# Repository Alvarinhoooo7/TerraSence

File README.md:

<div align="center">
  <picture>
    <source media="(prefers-color-scheme: dark)" srcset="Logo/Logo/terrasense-wordmark-dark.svg" />
    
  </picture>
</div>

# TerraSense

TerraSense es un proyecto de instrumento portátil y aplicación móvil para medir suelo y ambiente, interpretar las lecturas según la etapa del cultivo y orientar qué revisar en el campo. Está dirigido a agricultores y asesores que necesitan consultar y guardar mediciones, incluso donde no hay cobertura de internet.

**El proyecto está en desarrollo.** La app implementa la captura por Bluetooth, la evaluación local y el historial. El firmware ya lee la sonda de suelo por Modbus: en banco entregó 1.000 de 1.000 lecturas sin error de verificación de redundancia cíclica (31-10-2026), con la sonda al aire. Lo pendiente es la exactitud de esas lecturas en agua y en tierra, que se cierra con la campaña de laboratorio, y la validación en campo.

## Por qué TerraSense

TerraSense no es un sensor de suelo ni un nodo de monitoreo enterrado: es una **sonda portátil multivariable de diagnóstico agronómico**. Viaja con la persona, mide donde la persona decide y entrega diez variables del punto de medición en el mismo instante, terminando en una orientación o plan de acción según la fase del cultivo y la especie. Esa combinación es la que no existe en el mercado actual.

La propuesta se ordena en tres clases de valor, y conviene no mezclarlas porque cada una se sostiene con evidencia distinta: la **funcional** (qué permite hacer el instrumento que hoy no se puede), la **económica** (qué cuesta sostener esa información en el tiempo) y la **emocional** (qué incertidumbre le quita de encima al productor). El texto canónico de la propuesta, con esas tres clases y la clasificación de cada atributo en paridad o diferencia, vive en [el capítulo III del informe de la Evaluación 2](Evaluacion/Evaluacion%202/INFORME%202.md#la-propuesta-de-valor); lo que sigue es su resumen.

| | Laboratorio de suelos | Nodo fijo de monitoreo | Medidor portátil de 1 a 4 variables | **TerraSense** |
|---|---|---|---|---|
| Puntos que se pueden medir | sólo los que se pagan | uno por nodo instalado | cualquiera | **cualquiera, con su ubicación registrada** |
| Costo de la medición siguiente | el precio de otra muestra | otro nodo para cubrir otro punto | cero | **cero** |
| Variables por lectura | según el análisis contratado | las del nodo | 1 a 4 | **10: 7 del suelo y 3 del ambiente** |
| Qué recibe el agricultor | concentraciones trazables, en días | series de tiempo y alertas del punto | un valor numérico | **las diez variables con semáforo y un plan de acción por fase del cultivo** |
| Sin cobertura de internet | logística de envío | requiere red permanente | funciona | **mide, diagnostica, georreferencia y guarda** |
| Suscripción mensual | se paga por muestra | habitual en la plataforma | no | **ninguna, y las mediciones son del agricultor** |
| Memoria del punto medido | informes sueltos | del punto fijo | no deja registro | **historial con fecha, ubicación y evaluación** |

Las ventajas no son atributos declarados: son consecuencias de cómo está construido el sistema.

1. **Mide donde el agricultor decide.** El campo no es homogéneo. Un nodo fijo describe con mucho detalle un solo punto; una sonda portátil describe el campo entero. Es arquitectura, no una característica que se pueda igualar bajando el precio.
2. **Diez variables en una sola inserción.** Siete del suelo —humedad, temperatura, conductividad eléctrica, pH, nitrógeno, fósforo y potasio— y tres del ambiente —temperatura, humedad y presión del aire—, todas del mismo punto y del mismo instante. Los medidores portátiles con que se compara entregan entre tres y cuatro.
3. **Entrega un plan de acción, no un número.** El motor agronómico corre completo en el teléfono y traduce la medición en qué revisar, por qué y en qué orden. Un valor de conductividad no dice nada a quien no lo interpreta: la diferencia entre el dato y la decisión es todo el producto.
4. **La medición siguiente no cuesta nada.** Sin cobro por lectura ni suscripción, el costo marginal de volver a medir es cero. Eso cambia la conducta: se mide antes y después de fertilizar, en varios sectores, durante toda la temporada.
5. **Funciona sin cobertura.** Medir, diagnosticar, georreferenciar y guardar ocurren sin red; la nube sólo respalda después. En un campo sin señal, un producto que necesite conexión para interpretar no sirve.
6. **Deja memoria del campo.** Cada medición queda con su fecha, su ubicación y su evaluación, de modo que la segunda temporada se compara con la primera.

**Complemento del laboratorio, no su reemplazo.** Un análisis acreditado entrega concentraciones trazables de los puntos que se pagan, una o dos veces por temporada. TerraSense aporta lo que ese análisis no puede costear: la repetición. Medir el mismo punto antes y después de fertilizar, medir varios sectores el mismo día y repetir la lectura cuantas veces se quiera permite ponderar el comportamiento del campo sobre muchas mediciones, en lugar de inferirlo de una sola muestra. No tiene la exactitud del laboratorio en una medición aislada y no pretende tenerla: lo complementa, porque además termina donde el informe de laboratorio no llega, que es en un plan de acción según la fase del cultivo. Lo mismo vale para el asesor agronómico, cuyo criterio el equipo confirma o corrige con datos del propio suelo, y para el nodo fijo, que da continuidad en un punto mientras la sonda cubre el campo entero. El laboratorio fija el punto de referencia; TerraSense sigue su evolución entre un análisis y el siguiente.

**Qué nos diferencia y qué sólo nos iguala.** De los atributos del producto, cuatro son diferencia frente a toda la competencia comparable: la interpretación por etapa fenológica y especie, la orientación de manejo como salida del sistema, las diez variables de una sola inserción y la trazabilidad documental del criterio agronómico con su catálogo de cultivos chileno. Los demás integran el producto y se comunican como parte de él, nunca como su diferencia: la portabilidad es condición de la categoría, y la aplicación propia, la georreferenciación, el uso sin conexión y la ausencia de suscripción **también los ofrecen los medidores portátiles con que competimos**. La ausencia de suscripción es diferencia frente al laboratorio, que cobra por muestra, y frente al monitoreo remoto, que cobra plataforma mensual; no frente a Hanna ni a Bluelab, que tampoco cobran cuota. La clasificación completa está en la tabla de paridad y diferencia del [texto canónico](Evaluacion/Evaluacion%202/INFORME%202.md#la-propuesta-de-valor).

## Cómo funciona

1. **El equipo reúne las lecturas.** El diseño integra una sonda de suelo y un sensor ambiental BME280 con un ESP32 que se comunica con el teléfono por Bluetooth de bajo consumo (BLE).
2. **La app interpreta la medición.** El usuario elige la etapa del cultivo y, cuando corresponde, puede indicar la especie. El motor agronómico aplica reglas locales, explica las condiciones que requieren atención y señala lo que no puede evaluar con los datos disponibles.
3. **El resultado queda guardado.** La app conserva la lectura y su evaluación en el teléfono y las sincroniza con Supabase cuando hay conexión. Si el usuario incluye su ubicación, también puede consultar el pronóstico como apoyo para organizar labores.
4. **El backoffice permite dar soporte.** La cuenta de soporte administra equipos y accesos desde la web.

```mermaid
flowchart LR
    S[Sonda de suelo] -->|RS-485| E[ESP32]
    B[Sensor ambiental BME280] --> E
    E <-->|Bluetooth| A[App móvil]
    C[Servicio de pronóstico] -.->|Internet| A
    A <-->|Sincronización| D[(Supabase)]
    W[Backoffice de soporte] <--> D
```

La medición y la evaluación local están diseñadas para funcionar sin internet después de configurar la cuenta y vincular el equipo. El pronóstico, la gestión de accesos y el respaldo en la nube requieren conexión. Las recomendaciones son orientativas y dependen de la calidad de las lecturas y de los criterios disponibles para cada cultivo.

## Dónde encontrar cada parte

| Módulo | Qué contiene |
|---|---|
| [App móvil](App/README.md) | Funcionamiento de la app, flujo de pantallas, motor agronómico y puesta en marcha. |
| [Firmware](Firmware/README.md) | Programa del ESP32, comunicación con el teléfono y estado de integración de los sensores. |
| [Hardware](PCB/README.md) | Esquemáticos, placa electrónica, alimentación y carcasa. |
| [Backoffice web](Web/README.md) | Herramientas de soporte y ejecución de la web. |
| [Supabase](supabase/README.md) | Base de datos, autenticación, permisos y sincronización. |
| [Documentación](docs/README.md) | Informes, contratos técnicos y plan de validación. |

Para ejecutar el software, sigue la puesta en marcha de [App](App/README.md#desarrollo-local) o de [Web](Web/README.md). Cada módulo documenta su propia configuración.

Lo que llega a `main`, y cada pull request, pasa por el [workflow de verificación](.github/workflows/verificacion.yml): regenera el modelo financiero y corre sus pruebas, revisa los enlaces y diagramas de la documentación, y ejecuta las pruebas de la app y las del backoffice con su construcción. Además guarda dos reglas que no se deducen leyendo el código: que ningún archivo generado se haya editado a mano y que el informe entregable se lea sin acceso al repositorio.

<!-- FINANZAS:INICIO -->

## Modelo económico

El proyecto contempla la venta del equipo, con la app y la evaluación local sin suscripción. El precio se deriva de la estructura completa de costos y de la utilidad exigida por el modelo.

Los supuestos, el financiamiento y los resultados de viabilidad se consultan en el [modelo económico](docs/MODELO_ECONOMICO.md) y los [resultados financieros](docs/RESULTADOS_FINANCIEROS.md). Las cifras se regeneran con `python finanzas/modelo.py`.

<!-- FINANZAS:FIN -->

---

Proyecto de título de Ingeniería en Electrónica y Sistemas Inteligentes — INACAP.

Autores: Álvaro Villena y Alan Escobar.

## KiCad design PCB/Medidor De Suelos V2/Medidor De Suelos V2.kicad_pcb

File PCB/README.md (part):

# 🔌 TerraSense · PCB V2

Especificación del hardware del instrumento portátil de medición de suelo: placa portadora, árbol de alimentación, control y periféricos. Este documento es la fuente para dibujar el esquemático y rutear la placa.

> ### 🛑 Estado de verificación — leer antes de usar este documento
>
> **Describe un diseño en curso, no un producto verificado.** Las secciones 4 a 9 se escribieron antes de dibujar el esquemático y conservan designadores y nets antiguos: **cuando difieran, mandan el esquemático de KiCad y [`Firmware/pines.h`](../Firmware/pines.h)**. El mapa de pines de la sección 5.7 ya está alineado con ambos.
>
> | Afirmación | Estado real |
> | :--- | :--- |
> | Placa ruteada | **Sí.** Esquemático y ruteo en `Medidor De Suelos V2/`. Primer lote de 5 placas sin ensamblar pedido a JLCPCB; aún no se arma ni se prueba |
> | Firmware | **Existe en [`Firmware/`](../Firmware/README.md)**: vinculación BLE, LEDs, buzzer, trama de 20 bytes y lectura Modbus de la sonda, esta última sin ensayo en banco |
> | Mapa de registros de la sonda | **Coincide con el manual del fabricante** de la muestra adquirida (ComWinTop CWT-Soil-NPKPHCTH-S). Falta la captura real en banco |
> | BLE 5.0 | El ESP32-WROOM-32E especifica **Bluetooth 4.2 BR/EDR y BLE**. La certificación del módulo no acredita el equipo terminado |
> | Consumo en reposo y autonomía | **No se declaran en la V2.** Ver sección 5.9 |
> | IP67 y peso bajo 280 g | **Objetivos de diseño sin ensayo.** No hay actas ni pesaje del conjunto |
> | Sonda operando a 5 V | Solo puede afirmarse del **SKU y variante validados**, que aún no se adquieren |
>
> Las cifras de componentes y costos viven en la lista `bom` de [`finanzas/supuestos.json`](../finanzas/supuestos.json) y se publican en [`BOM_TerraSense.xlsx`](BOM_TerraSense.xlsx), que regenera `python finanzas/modelo.py`. **No editar ese Excel a mano.**

---

## 📑 Tabla de Contenidos

- [1. Alcance de la V2](#1-alcance-de-la-v2)
- [2. Especificaciones generales](#2-especificaciones-generales)
- [3. Arquitectura y nets del sistema](#3-arquitectura-y-nets-del-sistema)
- [4. Guía de Implementación del Esquemático](#4-guía-de-implementación-del-esquemático)
- [5. Puntos de prueba y medición](#5-puntos-de-prueba-y-medición)
- [6. Fabricación de la PCB y Diseño mecánico](#6-fabricación-de-la-pcb-y-diseño-mecánico)
- [7. Decisiones de Diseño y Detalles Técnicos (Rationale)](#7-decisiones-de-diseño-y-detalles-técnicos-rationale)
- [8. Orden de trabajo y pendientes](#8-orden-de-trabajo-y-pendientes)
- [9. Netlist completa](#9-netlist-completa)

---

## 1. Alcance de la V2

La V2 es una **placa portadora**: no integra el silicio, sino que sostiene y conecta tres módulos comerciales más la electrónica discreta que los une.

| Módulo | Qué aporta |
| :--- | :--- |
| DevKit ESP32-WROOM-32 | Microcontrolador, radio BLE, regulador de 3,3 V y USB-UART |
| **`LX-LCBST`**, PCB combinada USB-C | Carga de la celda con sus protecciones y elevación a 5,0 V |
| Módulo BME280 I²C | Temperatura del aire, humedad relativa y presión |

### 1.1. Decisiones cerradas

| Decisión | Valor | Motivo |
| :--- | :--- | :--- |
| Microcontrolador | **DevKit ESP32-WROOM-32**, no módulo desnudo | Evita rutear LDO, USB-UART y auto-reset en la portadora |
| Carga con el equipo apagado | **Sí** | Define dónde va `SW1`: después del módulo, nunca en serie con la celda |
| USB al exterior | **Solo el USB-C del módulo de carga** | El micro-USB de la DevKit queda interno |
| Tercer pin del conector de batería | **NC**, no conectado | |
| Divisor de batería | **Conmutado por MOSFET**, no fijo | Evita dejar tensión sobre una entrada sin alimentar |
| Consumo en reposo | **No se declara** | La DevKit consume miliamperios; `SW1` lo resuelve apagando |
| Trama BLE | **20 bytes, formato único** | Contrato de la sección 6.9 |

> La elección de DevKit es **propia de esta versión**. El proyecto está definido sobre el módulo WROOM-32 desnudo, que es lo que costea el BOM. Volver al módulo desnudo obliga a agregar a la portadora el regulador de 3,3 V, el USB-UART y el circuito de auto-reset.

### 1.2. Contenido de la carpeta

| Ruta | Qué es |
| :--- | :--- |
| `README.md` | Este documento |
| `BOM_TerraSense.xlsx` | Lista de materiales, **generada**; no editar a mano |
| `Medidor De Suelos V2/` | Proyecto KiCad de la V2: esquemático y ruteo. **Fuente de verdad del hardware** |
| `V1/` | Prototipo anterior, congelado. No se edita ni se usa como referencia de diseño |
| `V3/` | Placa del instrumento del informe 2 (90 × 64 mm): esquemático con circuitos integrados soldados y placa ruteada en dos capas con planos de masa. Local, fuera de git; no está liberada a fabricación |

Las vistas de la V3 y los anexos C y D se regeneran con `python finanzas/figuras_e2.py`, que toma los renders de la placa con `kicad-cli`. El estado eléctrico y mecánico pendiente está en el [plan de implementación del informe 2](<../Evaluacion/Evaluacion 2/PLAN DE IMPLEMENTACION.md>). La lista de materiales y los costos se mantienen por decisión del proyecto.

---

## 2. Especificaciones generales

| Parámetro | Valor de diseño | Justificación |
| :--- | :--- | :--- |
| **Microcontrolador** | DevKit ESP32-WROOM-32 | Doble núcleo a 240 MHz, 520 KB SRAM, 4 MB de flash. [Ficha Espressif](https://documentation.espressif.com/esp32-wroom-32e_esp32-wroom-32ue_datasheet_en.html): **Bluetooth 4.2 BR/EDR y BLE**, no 5.0 |
| **Sonda de suelo** | Industrial 7 en 1, RS-485 Modbus RTU | ComWinTop CWT-Soil-NPKPHCTH-S. Alimentación **4,5 – 30 V DC**, 0,5 W como máximo a 24 V, IP68, cable de 2 m; electrodos de aleación anticorrosión, grado de acero por confirmar |
| **Alimentación de la sonda** | **5,0 V DC** conmutados | Operación directa sin elevar a 12 V; menor estrés térmico y menor consumo |
| **Sensor ambiental** | BME280 I²C a 3,3 V | Temperatura del aire, humedad relativa y presión en el punto de lectura |
| **Transceptor de bus** | SP3485 a 3,3 V | Diferencial industrial semidúplex, sin desplazadores de nivel |
| **Batería** | LiPo 1S 3,7 V, 2.000 mAh con PCM | Formato prismático plano, ~35 g, sin portaceldas |
| **Carga y elevación** | Módulo **`LX-LCBST`** | Resuelve carga, protección y elevación a 5 V en un submódulo |
| **Encendido** | Interruptor rocker SPST | Corta el consumo entre usos |
| **Formato** | Instrumento portátil de mano | Inserción manual directa en el suelo |

---

## 3. Arquitectura y nets del sistema

```text
 ┌─────────────────────────────────────────────────────────────────────────────┐
 │                    DIAGRAMA DE BLOQUES — TerraSense V2                      │
 └─────────────────────────────────────────────────────────────────────────────┘

   [ USB-C exterior ]
          │
          ▼
  ┌───────────────────────────────┐        ┌──────────────────────────┐
  │  MOD1  LX-LCBST carga+boost   │◄───────┤ BT1 LiPo 1S 2000 mAh     │
  │  • Cargador con protecciones  │  VBAT  │ P1 / P2 pads soldados    │
  │  • Elevador 3,7 V ──► 5,0 V   │────────┤ F1 fusible 1 A · JP1     │
  │                               │        │ D1 M7 crowbar a GND      │
  └───────────────┬───────────────┘        └──────────────────────────┘
                  │ 5 V
                  ▼
            [ SW1 rocker ]
                  │
                  ▼  +5V ──────────────────────────────┐
  ┌───────────────┴───────────────┐                    │
  │  U1  DevKit ESP32-WROOM-32    │                    ▼
  │  VIN ◄── +5V   (C3, C4)       │          [ Q1 P-MOSFET power gate ]
  │  3V3 ──► +3V3  (C5, C6)       │             (mandado por GPIO5 vía Q2)
  └──┬─────────────┬──────────┬───┘                    │
     │             │          │                        ▼  5V_SONDA
     │ I²C         │ UART2    │ ADC                    │
     ▼             ▼          ▼                        │
 [ U3 BME280 ]  [ U2 SP3485 ] [ Divisor R9/R10 ]       │
       3V3         3V3          conmutado por Q3       │
                    │ A/B                              │
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
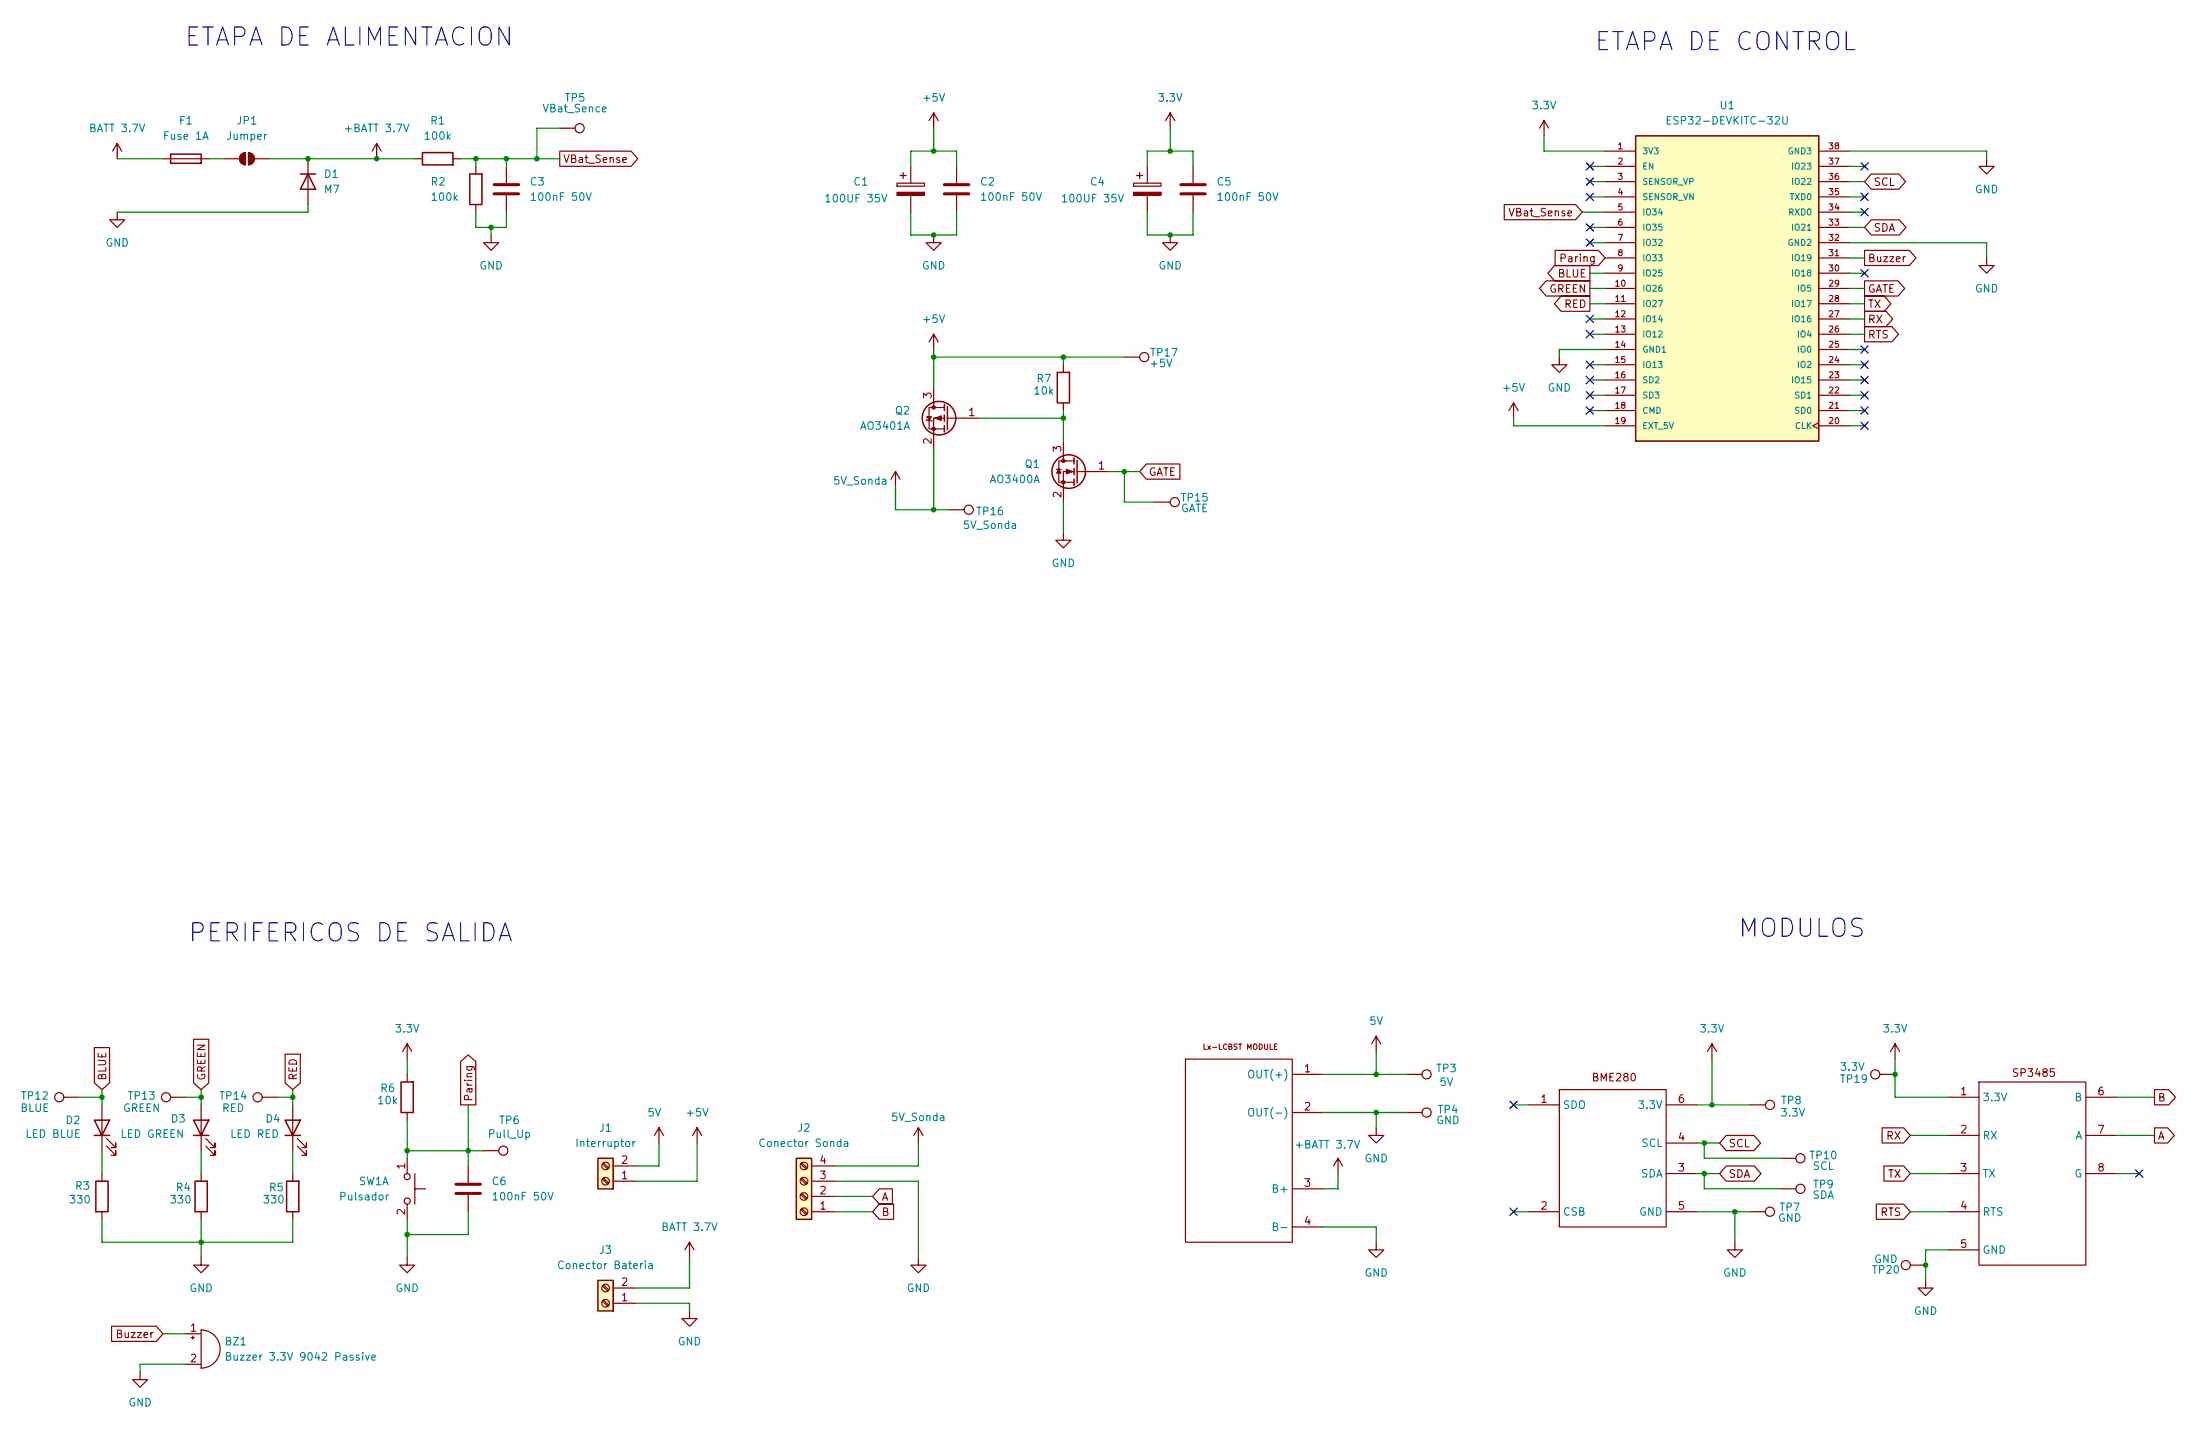
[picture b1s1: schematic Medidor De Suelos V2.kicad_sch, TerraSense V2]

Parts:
BZ1: Buzzer 3.3V 9042 Passive; MagneticBuzzer_CUI_CST-931RP-A
C1, C4: 100UF 35V; CP_Elec_6.3x7.7
C2, C3, C5, C6: 100nF 50V; C_1206_3216Metric_Pad1.33x1.80mm_HandSolder
D1: M7; D_SMA
D2: LED BLUE; LED_0603_1608Metric_Pad1.05x0.95mm_HandSolder
D3: LED GREEN; LED_0603_1608Metric_Pad1.05x0.95mm_HandSolder
D4: LED RED; LED_0603_1608Metric_Pad1.05x0.95mm_HandSolder
F1: Fuse 1A; Fuse_0603_1608Metric
J1: Interruptor; TerminalBlock_MetzConnect_Type055_RT01502HDWU_1x02_P5.00mm_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
J2: Conector Sonda; TerminalBlock_MetzConnect_Type055_RT01504HDWU_1x04_P5.00mm_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
J3: Conector Bateria; TerminalBlock_MetzConnect_Type055_RT01502HDWU_1x02_P5.00mm_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
JP1: Jumper; SolderJumper-2_P1.3mm_Open_Pad1.0x1.5mm
MOD1: Modulo de Carga y Boost; Modulo_LX-LCBST
Q1: AO3400A; SOT-23_Handsoldering
Q2: AO3401A; SOT-23_Handsoldering
R1, R2: 100k; R_1206_3216Metric_Pad1.30x1.75mm_HandSolder
R3, R4, R5: 330; R_1206_3216Metric_Pad1.30x1.75mm_HandSolder
R6, R7: 10k; R_1206_3216Metric_Pad1.30x1.75mm_HandSolder
SW1: Pulsador; SW_Push_1P1T_XKB_TS-1187A
TP3: 5V; Pin_D1.0mm_L10.0mm_LooseFit
TP4, TP7, TP20: GND; Pin_D1.0mm_L10.0mm_LooseFit
TP5: VBat_Sence; Pin_D1.0mm_L10.0mm_LooseFit
TP6: Pull_Up; Pin_D1.0mm_L10.0mm_LooseFit
TP8, TP19: 3.3V; Pin_D1.0mm_L10.0mm_LooseFit
TP9: SDA; Pin_D1.0mm_L10.0mm_LooseFit
TP10: SCL; Pin_D1.0mm_L10.0mm_LooseFit
TP12: BLUE; Pin_D1.0mm_L10.0mm_LooseFit
TP13: GREEN; Pin_D1.0mm_L10.0mm_LooseFit
TP14: RED; Pin_D1.0mm_L10.0mm_LooseFit
TP15: GATE; Pin_D1.0mm_L10.0mm_LooseFit
TP16: 5V_Sonda; Pin_D1.0mm_L10.0mm_LooseFit
TP17: +5V; Pin_D1.0mm_L10.0mm_LooseFit
U1: ESP32-DEVKITC-32U; MODULE_ESP32-DEVKITC-32U; PARTREV V4
U2: BME280
U3: SP3485

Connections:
3.3V: C4.1, C5.1, R6.2, TP8.1, TP19.1, U1.1 (3V3), U2.6 (3.3V), U3.1 (3.3V)
5V: J1.2, MOD1.1 (OUT(+)), TP3.1
5V_Sonda: J2.4, Q2.2 (S), TP16.1
+5V: C1.1, C2.1, J1.1, Q2.3 (D), R7.2, TP17.1, U1.19 (EXT_5V)
+BATT 3.7V: D1.1 (K), JP1.2 (B), MOD1.3 (B+), R1.1
A: J2.2, U3.7 (A)
B: J2.1, U3.6 (B)
BATT 3.7V: F1.1, J3.2
BLUE: D2.2 (A), TP12.1, U1.9 (IO25)
Buzzer: BZ1.1 (+), U1.31 (IO19)
GATE: Q1.1 (G), TP15.1, U1.29 (IO5)
GND: BZ1.2 (-), C1.2, C2.2, C3.2, C4.2, C5.2, C6.2, D1.2 (A), J2.3, J3.1, MOD1.2 (OUT(-)), MOD1.4 (B-), Q1.2 (S), R2.1, R3.2, R4.1, R5.1, SW1.2 (D), TP4.1, TP7.1, TP20.1, U1.14 (GND1), U1.32 (GND2), U1.38 (GND3), U2.5 (GND), U3.5 (GND)
GREEN: D3.2 (A), TP13.1, U1.10 (IO26)
unnamed: D2.1 (K), R3.1
unnamed: D3.1 (K), R4.2
unnamed: D4.1 (K), R5.2
unnamed: F1.2, JP1.1 (A)
unnamed: Q1.3 (D), Q2.1 (G), R7.1
Paring: C6.1, R6.1, SW1.1 (C), TP6.1, U1.8 (IO33)
RED: D4.2 (A), TP14.1, U1.11 (IO27)
RTS: U1.26 (IO4), U3.4 (RTS)
RX: U1.27 (IO16), U3.2 (RX)
SCL: TP10.1, U1.36 (IO22), U2.4 (SCL)
SDA: TP9.1, U1.33 (IO21), U2.3 (SDA)
TX: U1.28 (IO17), U3.3 (TX)
VBat_Sense: C3.1, R1.2, R2.2, TP5.1, U1.5 (IO34)

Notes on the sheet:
PERIFERICOS DE SALIDA
ETAPA DE CONTROL
MODULOS
ETAPA DE ALIMENTACION

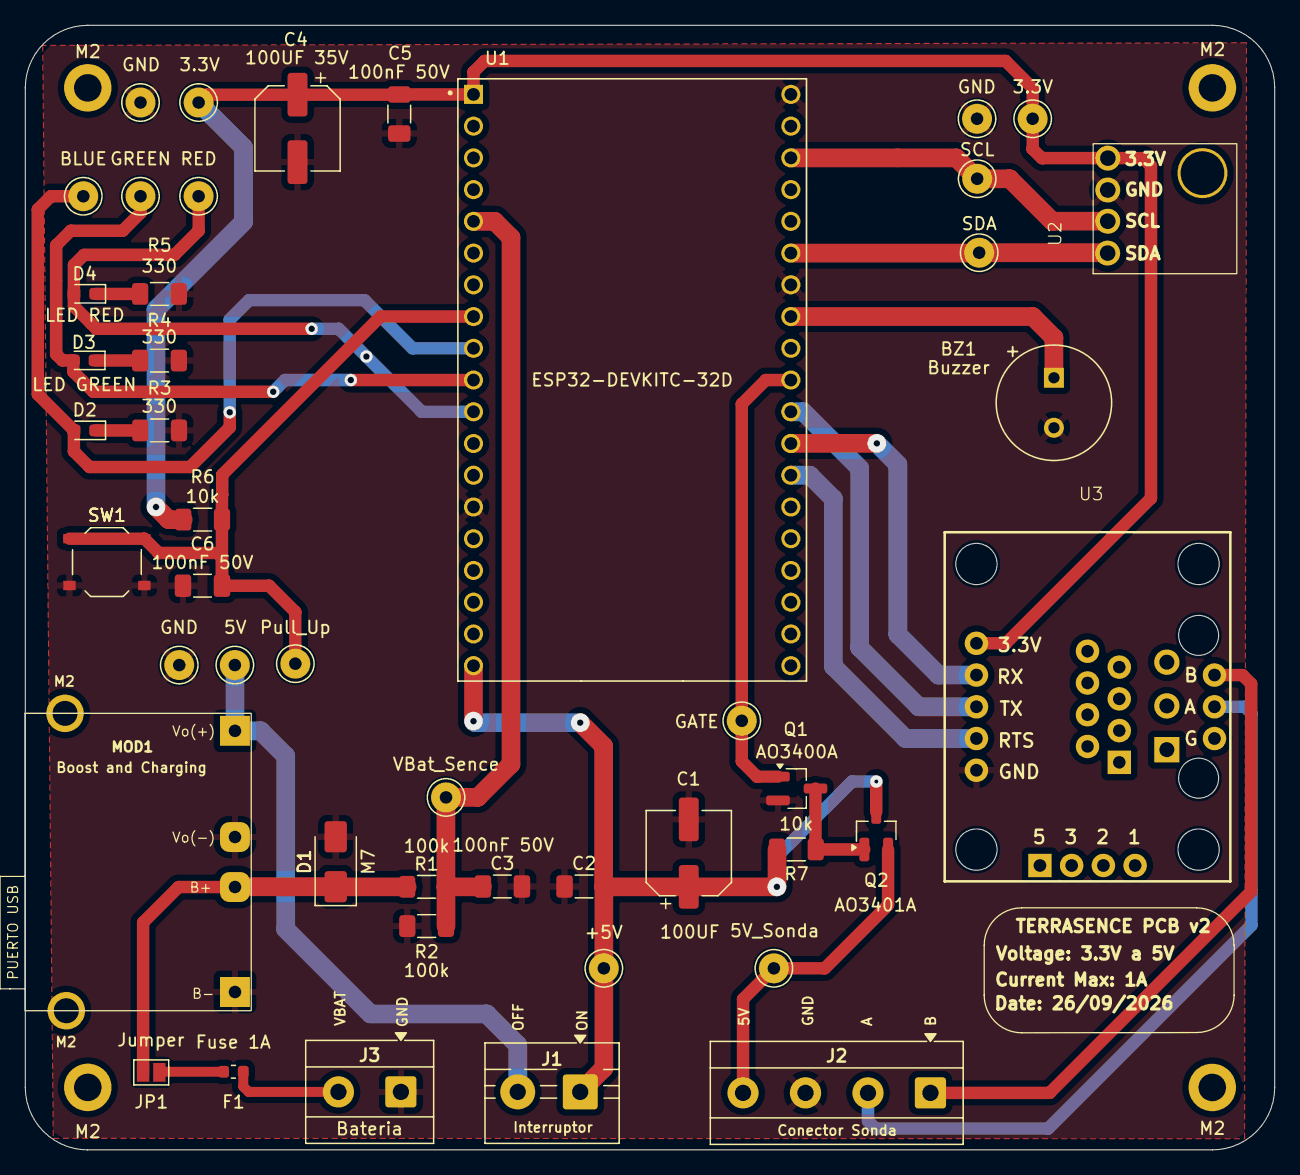
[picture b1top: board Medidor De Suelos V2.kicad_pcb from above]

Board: 2 copper layers, 100.0 x 90.0 mm, 50 parts (0 on the bottom side), 26 nets.

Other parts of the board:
M2, M2#2, M2#3, M2#4: MountingHole_2.2mm_M2_DIN965_Pad

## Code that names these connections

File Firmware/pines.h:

// pines.h
//
// Asignación de pines del ESP32-DevKitC con módulo WROOM-32D según el
// esquemático «Medidor De Suelos V2». En WROOM, IO16/IO17 están libres; en un
// WROVER los ocupa la PSRAM y este mapa no serviría.

#pragma once

// Batería (ADC1: no entra en conflicto con la radio BLE)
#define PIN_VBAT_SENSE 34

// Interfaz de usuario: pulsador PAIR (activo en LOW) y LEDs (activos en HIGH)
#define PIN_PARING     33
#define PIN_LED_BLUE   25
#define PIN_LED_GREEN  26
#define PIN_LED_RED    27

// Buzzer pasivo 9042 (BZ1), directo entre el pin y GND. Ver TASK.md, pendiente H1.
#define PIN_BUZZER     19

// Bus I2C (BME280)
#define PIN_SCL        22
#define PIN_SDA        21

// Alimentación de la sonda y UART / RS-485
// IO5 es pin de arranque (strapping): durante el reset puede emitir una señal
// antes de que setup() lo fije en LOW. Ver TASK.md, pendientes de hardware.
#define PIN_GATE       5
#define PIN_TX         17
#define PIN_RX         16
#define PIN_RTS        4
